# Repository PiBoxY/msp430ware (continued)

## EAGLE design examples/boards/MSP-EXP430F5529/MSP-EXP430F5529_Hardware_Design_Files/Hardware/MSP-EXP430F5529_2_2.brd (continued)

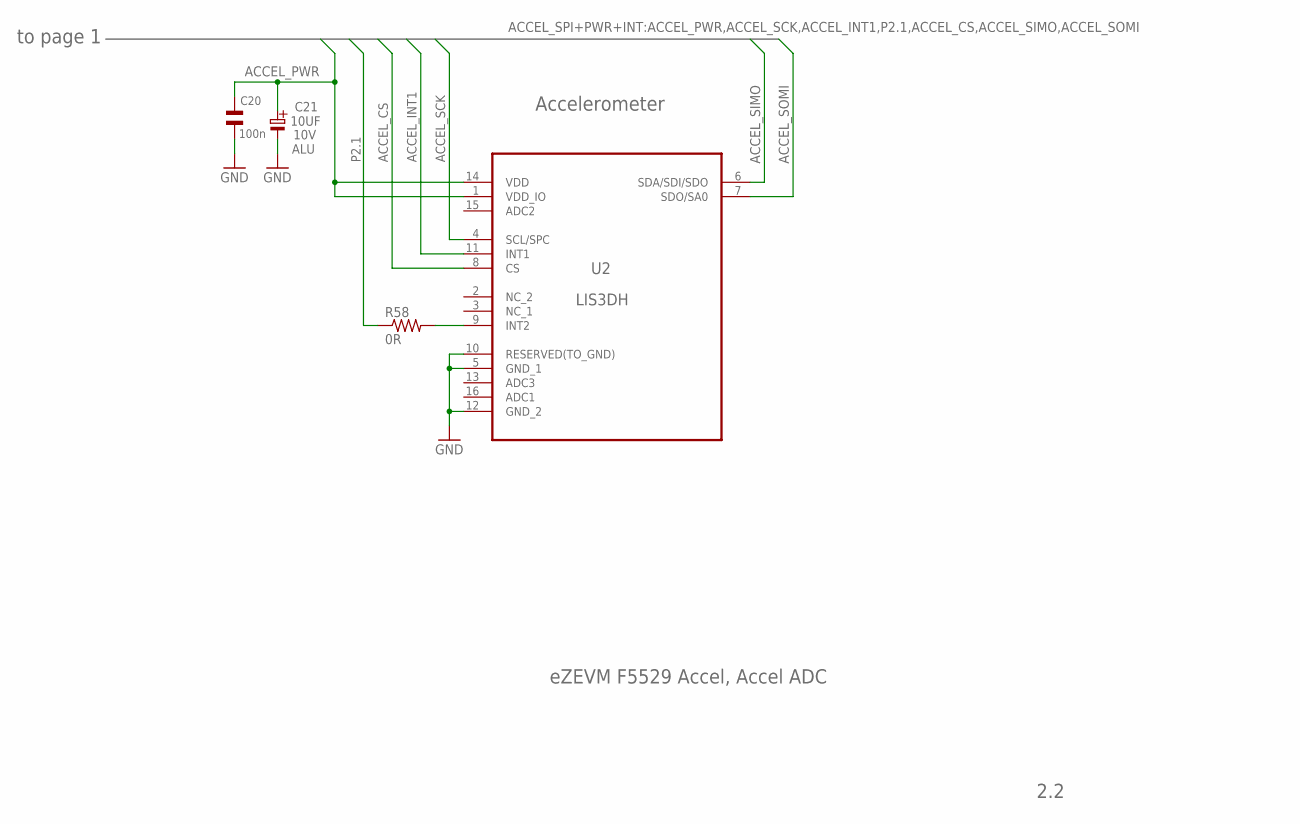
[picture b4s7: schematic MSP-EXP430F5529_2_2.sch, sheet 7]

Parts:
C20: 100n; 0402
C21: 10UF; ELKO_B; MPN EEE1AA100NR
R58: 0R; R0603
U2: LIS3DH; LGA16R50P3X5_300X300X100

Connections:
ACCEL_CS: U2.8 (CS); also elsewhere on the board
ACCEL_INT1: U2.11 (INT1); also elsewhere on the board
ACCEL_PWR: C20.2, C21.+, U2.1 (VDD_IO), U2.14 (VDD); also elsewhere on the board
ACCEL_SCK: U2.4 (SCL/SPC); also elsewhere on the board
ACCEL_SIMO: U2.6 (SDA/SDI/SDO); also elsewhere on the board
ACCEL_SOMI: U2.7 (SDO/SA0); also elsewhere on the board
GND: C20.1, C21.-, U2.5 (GND_1), U2.10 (RESERVED(TO_GND)), U2.12 (GND_2); also elsewhere on the board
unnamed: R58.2, U2.9 (INT2)
P2.1: R58.1; also elsewhere on the board

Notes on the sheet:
2.2
eZEVM F5529 Accel, Accel ADC
Accelerometer
to page 1

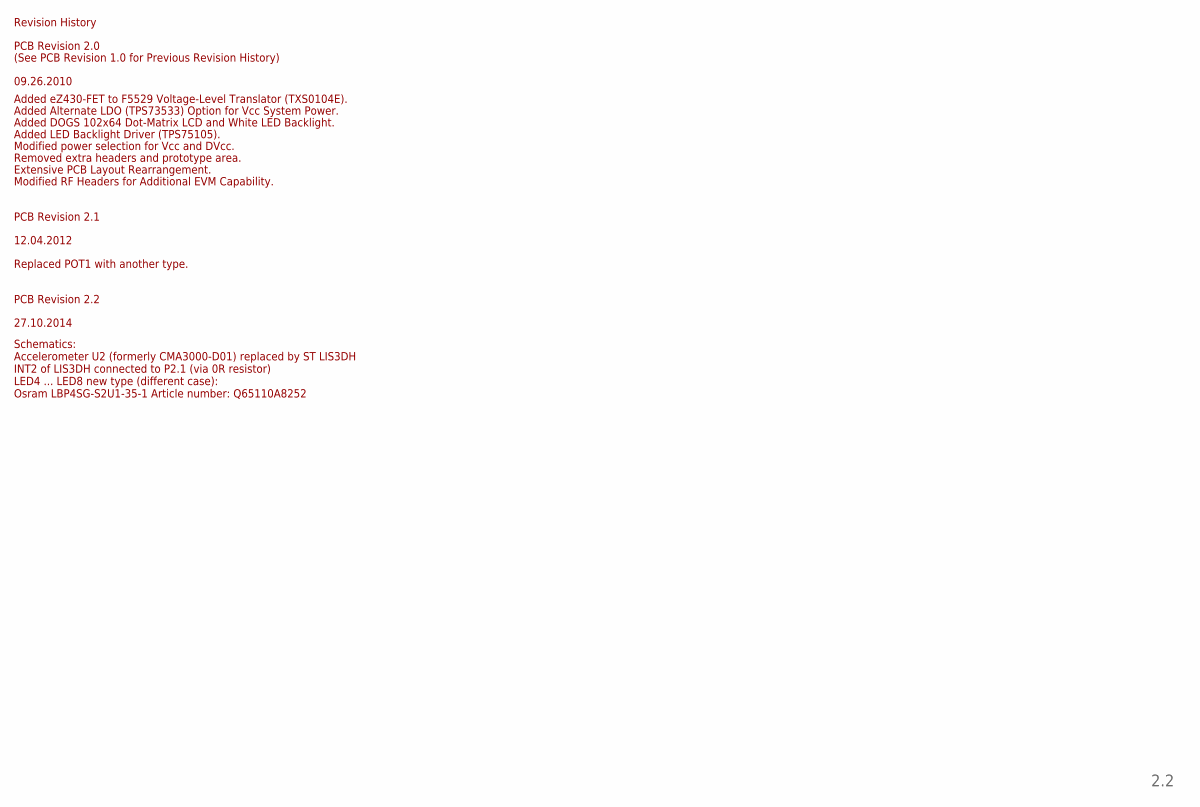
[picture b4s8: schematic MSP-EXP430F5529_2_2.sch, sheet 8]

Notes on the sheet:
Revision History
09.26.2010
PCB Revision 2.0
(See PCB Revision 1.0 for Previous Revision History)
2.2
Added eZ430-FET to F5529 Voltage-Level Translator (TXS0104E).
Added DOGS 102x64 Dot-Matrix LCD and White LED Backlight.
Modified power selection for Vcc and DVcc.
Removed extra headers and prototype area.
Added Alternate LDO (TPS73533) Option for Vcc System Power.
Added LED Backlight Driver (TPS75105).
Extensive PCB Layout Rearrangement.
Modified RF Headers for Additional EVM Capability.
PCB Revision 2.1
12.04.2012
Replaced POT1 with another type.
PCB Revision 2.2
27.10.2014
Schematics: Accelerometer U2 (formerly CMA3000-D01) replaced by ST LIS3DH INT2 of LIS3DH connected to P2.1 (via 0R resistor) LED4 ... LED8 new type (different case): Osram LBP4SG-S2U1-35-1 Article number: Q65110A8252

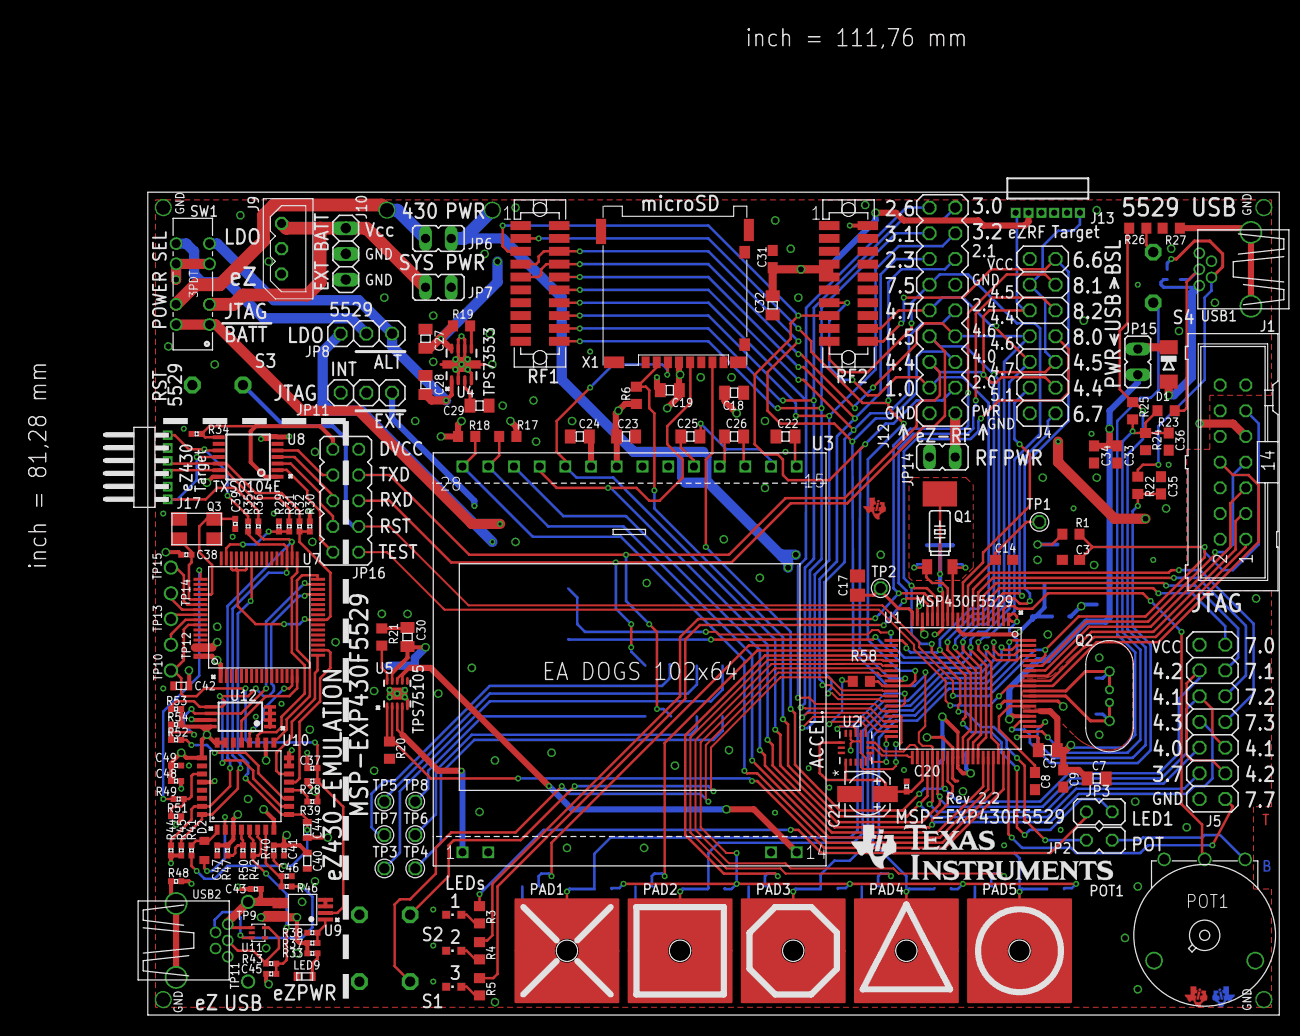
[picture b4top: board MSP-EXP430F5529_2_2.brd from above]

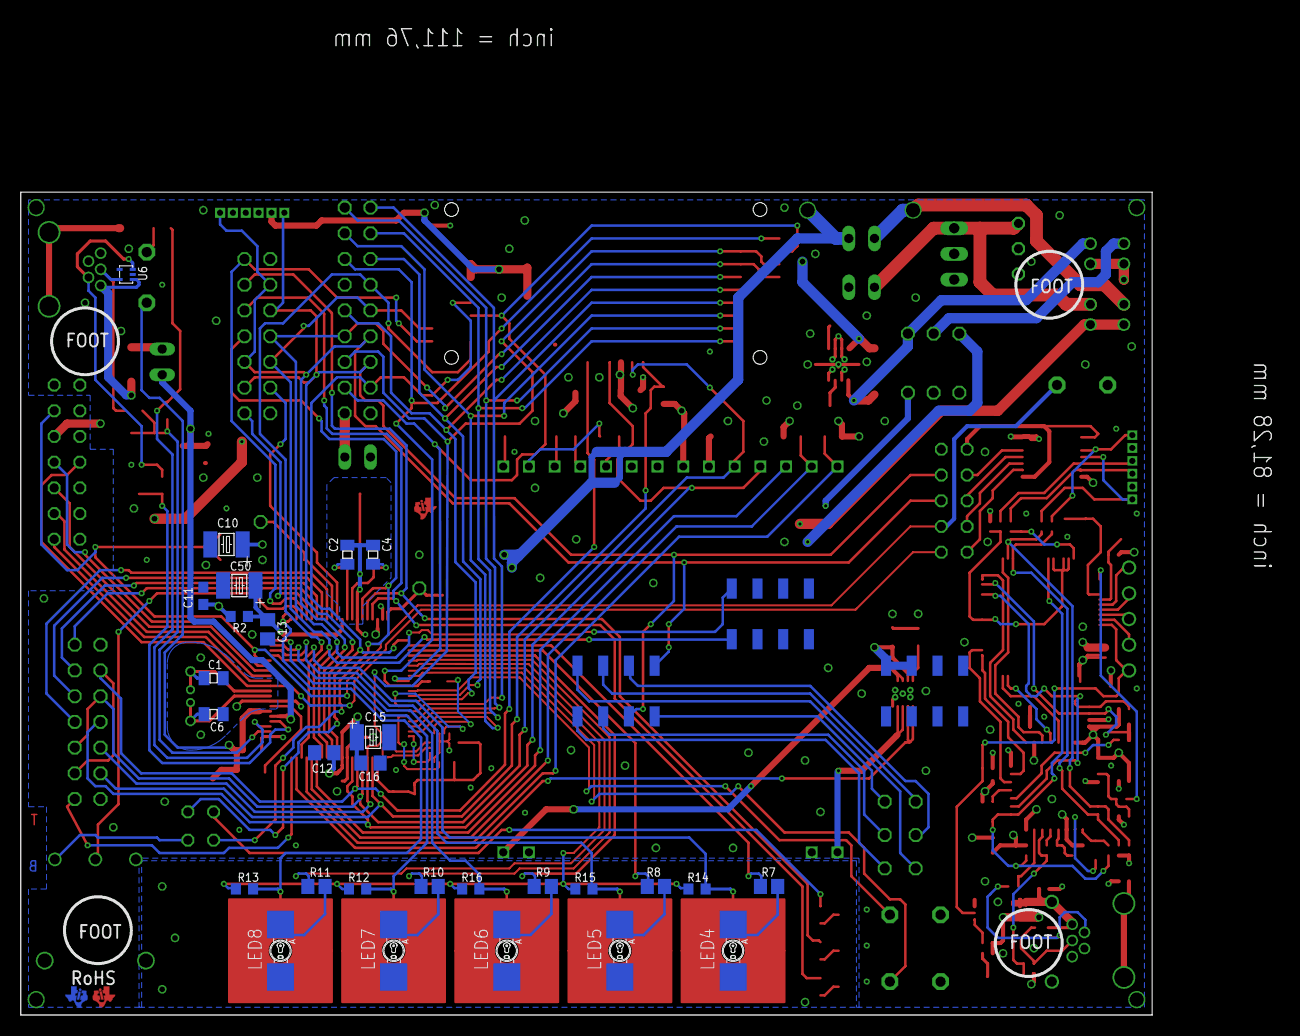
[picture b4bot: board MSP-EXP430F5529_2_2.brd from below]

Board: 4 copper layers, 124.3 x 98.2 mm, 186 parts (32 on the bottom side), 164 nets.

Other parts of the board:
U$1, U$3, U$4: MSP430_LAB_TILOGO_SMALL
U$2: LOGO2008_TPLACE

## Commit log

2019-02-06 v:3.80.06.03
